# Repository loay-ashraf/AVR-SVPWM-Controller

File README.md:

# AVR SVPWM Controller
SVPWM controller prototype implemented using AVR 8-bit microcontroller as a part of EV car conversion graduation project for Mechatronics Engineering Bachelor - Fall 2018.

## Overview
This section gives an overview of the system.

### Concept
Space vector pulse width modulation (SVPWM) is an algorithm for the control of pulse width modulation (PWM).

It is used for the creation of alternating current (AC) waveforms; most commonly to drive 3 phase AC powered motors at varying speeds from DC using multiple MOSFET/IGBT transistors. 

### System Layout
System is divided into two separate modules that communicate with each other to acheive the desired output, which are:

#### Pilot Module

Pilot module receives operating parameters from co-pilot (output frequency) and then outputs PWM signals to IGBT bridge, also it checks for current fault signal and in case of current overload it shuts down waiting for a manual reset.

#### Co-Pilot Module

Co-Pilot module reads user input via rotary potentiometer for output frequency, current sensor for current overload signal, then sends operating parameters to Pilot module and finally outputs system status (frequency, RPM, current,...etc.) to a character LCD.

## Discussion
This section discusses desicions made regarding design and implementation.

### Microcontroller

1. We opted for ATmega128 for pilot module as it runs at 16MHZ frequency and also has two 16-bit timers each having three output compare pins.
2. We opted for ATmega32 for co-pilot module as it runs at 16MHZ frequency and has enough pins for interfacing character LCD and current sensors via ADC.

### Communication Protocol

It is found that best communcation type (protocol) for such system would be a parallel communication bus because of the following reasons:

- Distance between modules is so short (<5m)
- Data sent is time senstive
- Pilot module is starving for CPU clock cycles to calculate and update timer's compare registers values and going with parallel would be ideal for this situation as it only costs one CPU clock cycle to read PINx register 

So we opted for an 8-bit wide parallel communication bus (including READY and ACK signals) which would be much faster than any serial communication available (USART, I2C and SPI).

### Timer Mode

We used Phase and Frequency correct PWM mode with ICR1 as TOP value as it mimics the center aligned PWM mode required for the space vector algorithm.

## Sample Output

### Non-Filtered Output

Below is the ouput of the system without attaching low pass LC filter:

### Filtered Output

Below is the output of the system with low pass LC filter attached:

## Built With
- Atmel Studio 7 - The official AVR IDE
- AVR-gcc V5.4 - C compiler
- GNU Make - auto-generated makefile
- CadSoft EAGLE - PCB design tool

## Authors
Loay Ashraf - <loay.ashraf.96@gmail.com>

Mohamed Gamal - <muhammed.gamal051@gmail.com>

## License
This project is licensed under the MIT License - see the LICENSE.md file for details

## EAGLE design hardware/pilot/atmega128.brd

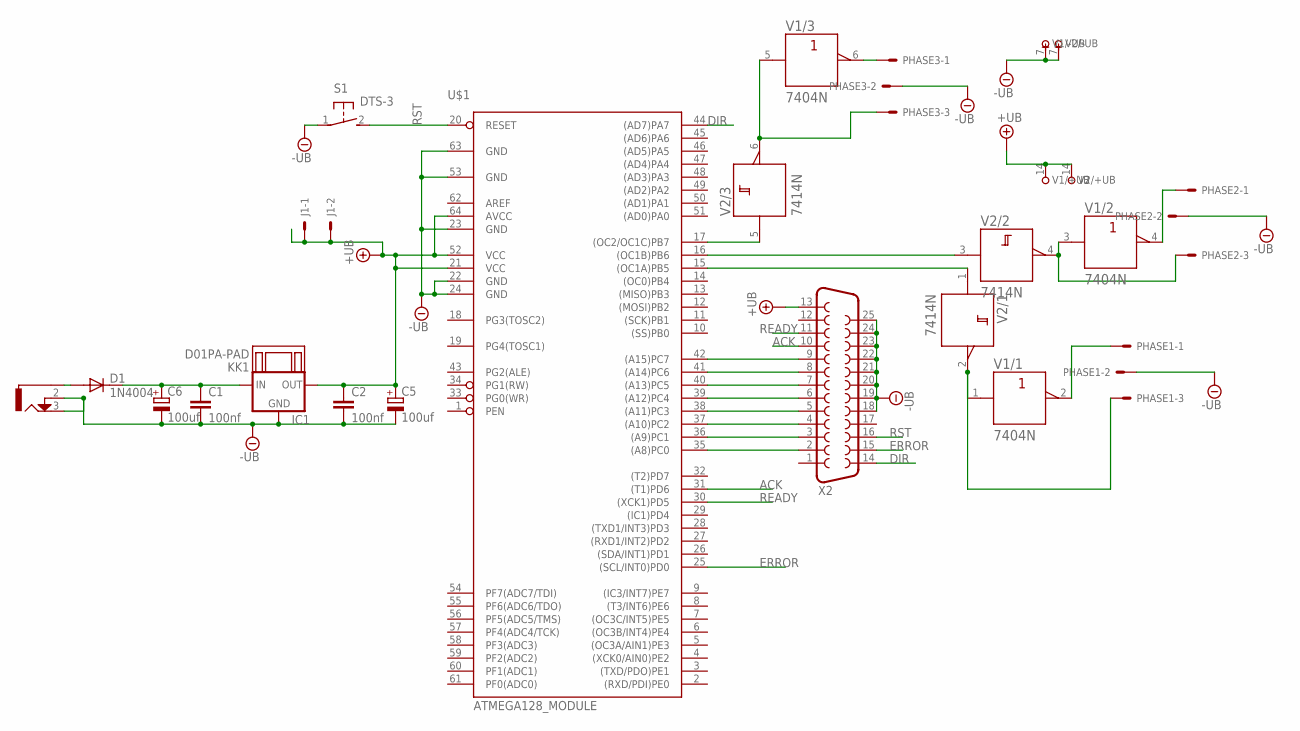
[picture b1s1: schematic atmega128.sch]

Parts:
C1, C2: 100nf; C025-025X050
C5, C6: 100uf; E2,5-6
D1: 1N4004; DO41-10
IC1: 78XXS
J1: 22-27-2021-02; 6410-02
KK1: D01PA-PAD
PHASE1, PHASE2, PHASE3: 6410-03
S1: DTS-3
U$1: ATMEGA128_MODULE
U$2: DC-21MM
V1: 7404N; DIL14
V2: 7414N; DIL14
X2: F25HP

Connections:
+UB: C2.1, C5.+, IC1.OUT, J1.1, J1.2, U$1.21 (VCC), U$1.52 (VCC), U$1.64 (AVCC), V1.14 (+UB), V2.14 (+UB), X2.13
-UB: C1.2, C2.2, C5.-, C6.-, IC1.GND, PHASE1.2, PHASE2.2, PHASE3.2, S1.1, U$1.22 (GND), U$1.23 (GND), U$1.24 (GND), U$1.53 (GND), U$1.63 (GND), U$2.2, U$2.3, V1.7 (-UB), V2.7 (-UB), X2.18, X2.19, X2.20, X2.21, X2.22, X2.23, X2.24, X2.25
ACK: U$1.31 ((T1)PD6), X2.10
DIR: U$1.44 ((AD7)PA7), X2.14
ERROR: U$1.25 ((SCL/INT0)PD0), X2.15
unnamed: D1.A, U$2.1
unnamed: C1.1, C6.+, D1.C, IC1.IN
unnamed: U$1.42 ((A15)PC7), X2.9
unnamed: U$1.41 ((A14)PC6), X2.8
unnamed: U$1.40 ((A13)PC5), X2.7
unnamed: U$1.39 ((A12)PC4), X2.6
unnamed: U$1.38 ((A11)PC3), X2.5
unnamed: U$1.37 ((A10)PC2), X2.4
unnamed: U$1.36 ((A9)PC1), X2.3
unnamed: U$1.35 ((A8)PC0), X2.2
PHASE1: U$1.15 ((OC1A)PB5), V2.1 (A)
PHASE1HIGH: PHASE1.1, V1.2 (Y)
PHASE1LOW: PHASE1.3, V1.1 (A), V2.2 (Y)
PHASE2: U$1.16 ((OC1B)PB6), V2.3 (A)
PHASE2HIGH: PHASE2.1, V1.4 (Y)
PHASE2LOW: PHASE2.3, V1.3 (A), V2.4 (Y)
PHASE3: U$1.17 ((OC2/OC1C)PB7), V2.5 (A)
PHASE3HIGH: PHASE3.1, V1.6 (Y)
PHASE3LOW: PHASE3.3, V1.5 (A), V2.6 (Y)
READY: U$1.30 ((XCK1)PD5), X2.11
RST: S1.2, U$1.20 (RESET), X2.16

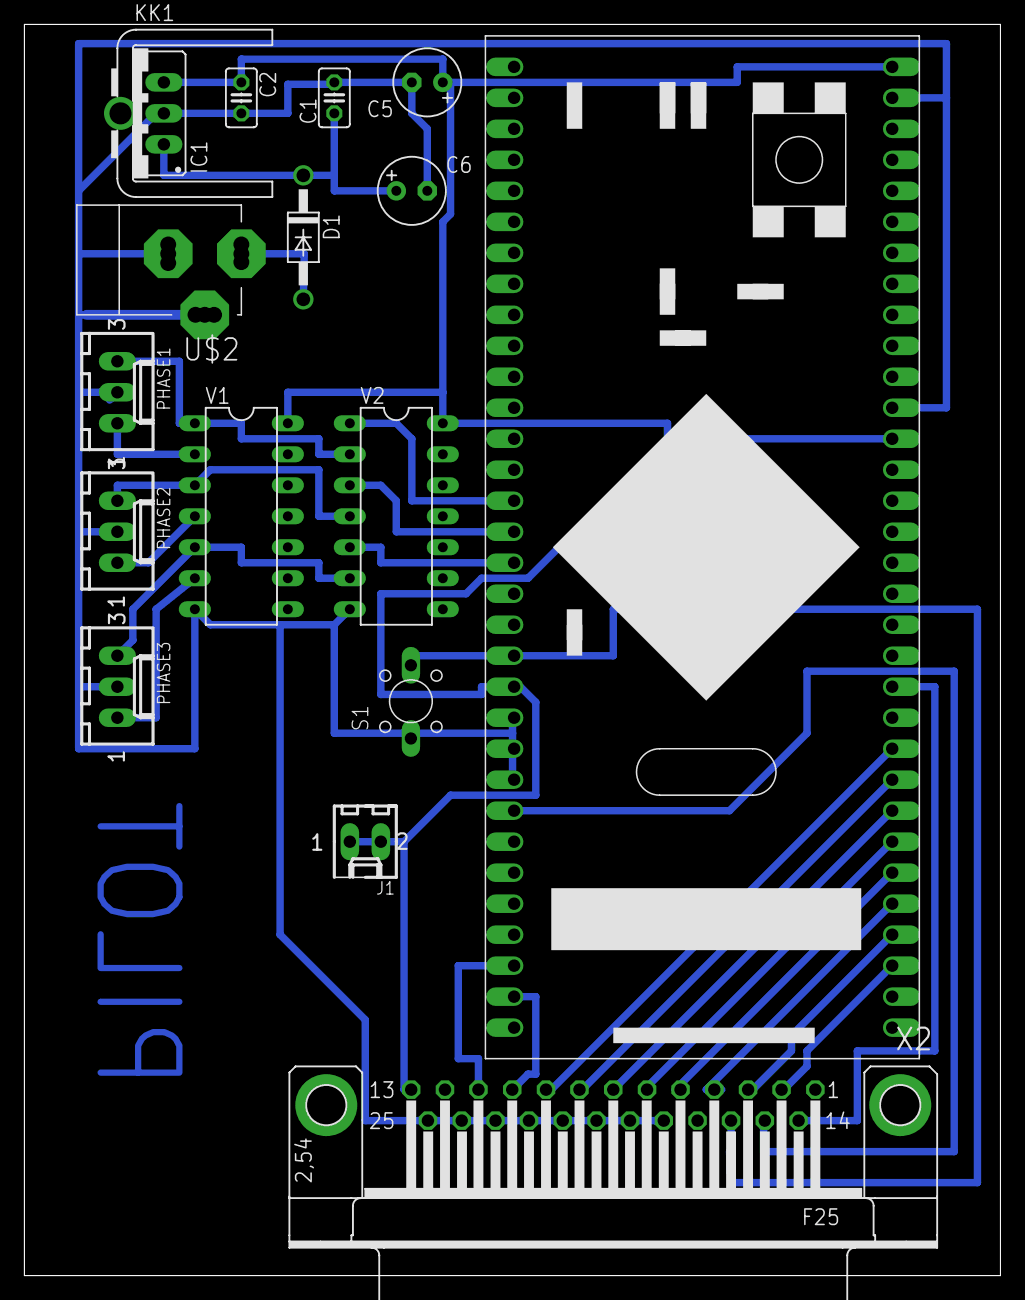
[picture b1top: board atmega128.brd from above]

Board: 2 copper layers, 80.0 x 102.5 mm, 17 parts (0 on the bottom side), 26 nets.

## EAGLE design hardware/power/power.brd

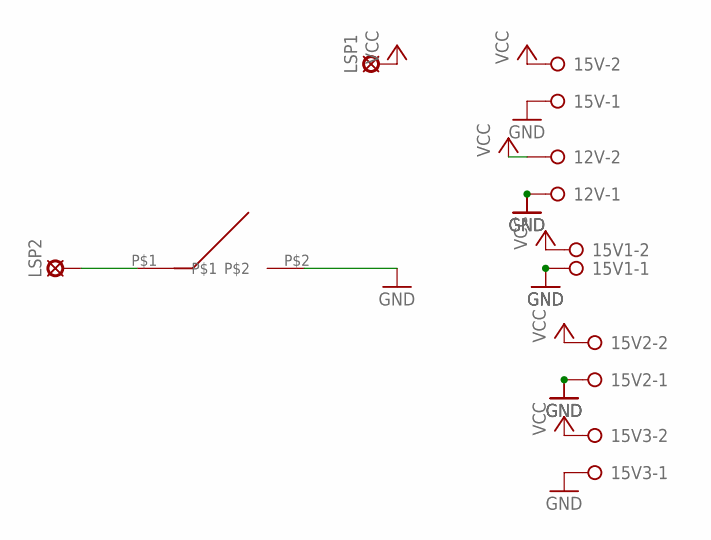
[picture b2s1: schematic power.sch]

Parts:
12V, 15V, 15V1, 15V2, 15V3: W237-02P; W237-132
LSP1, LSP2: SE14
U$1: ON/OFF

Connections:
GND: 12V.1, 15V.1, 15V1.1, 15V2.1, 15V3.1, U$1.P$2
unnamed: LSP2.MP, U$1.P$1
VCC: 12V.2, 15V.2, 15V1.2, 15V2.2, 15V3.2, LSP1.MP

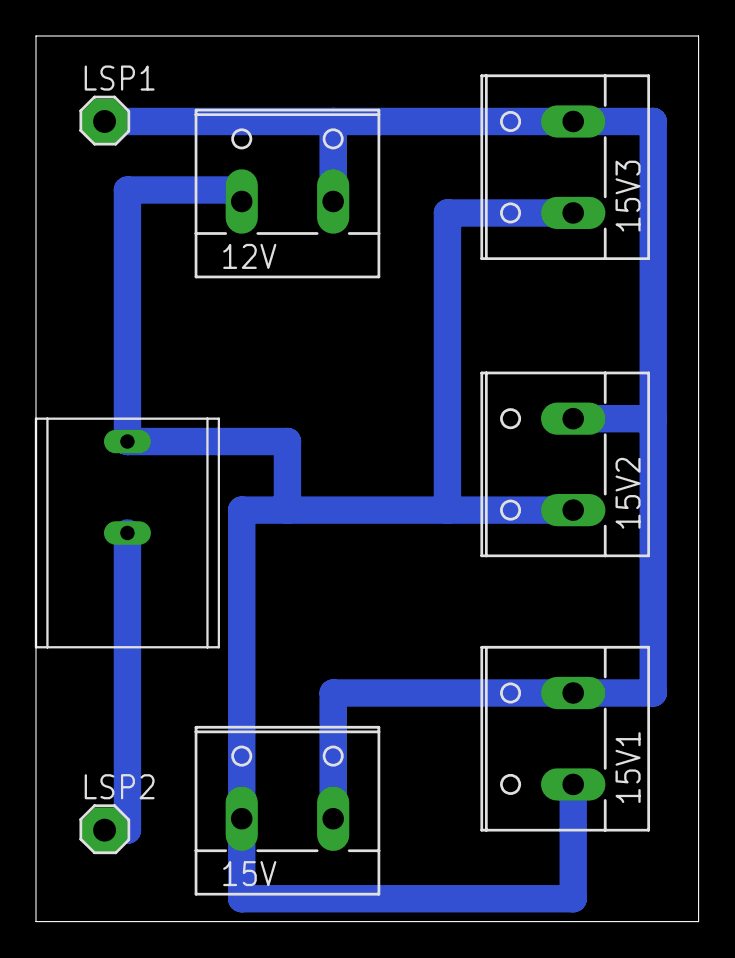
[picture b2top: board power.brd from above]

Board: 2 copper layers, 36.8 x 49.2 mm, 8 parts (0 on the bottom side), 3 nets.

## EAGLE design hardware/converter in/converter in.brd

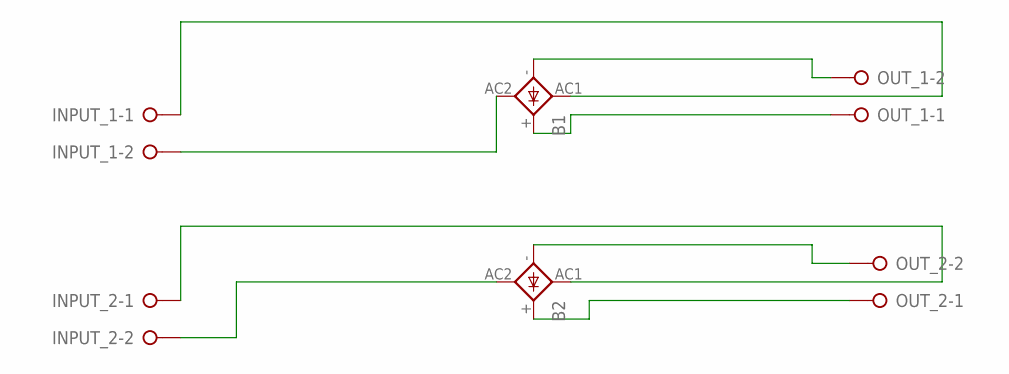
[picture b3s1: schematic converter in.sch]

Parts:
B1, B2: 2KBP
INPUT_1, INPUT_2: W237-02P; W237-132
OUT_1, OUT_2: W237-02P; W237-132

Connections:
unnamed: B1.-, OUT_1.2
unnamed: B1.+, OUT_1.1
unnamed: B2.-, OUT_2.2
unnamed: B2.+, OUT_2.1
unnamed: B2.AC1, INPUT_2.1
unnamed: B2.AC2, INPUT_2.2
unnamed: B1.AC2, INPUT_1.2
unnamed: B1.AC1, INPUT_1.1

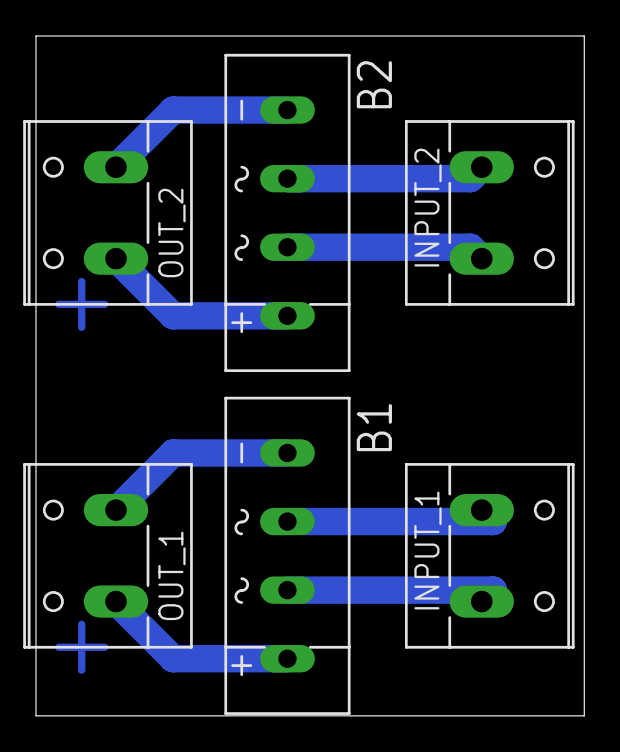
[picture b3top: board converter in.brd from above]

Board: 2 copper layers, 30.5 x 37.8 mm, 6 parts (0 on the bottom side), 8 nets.

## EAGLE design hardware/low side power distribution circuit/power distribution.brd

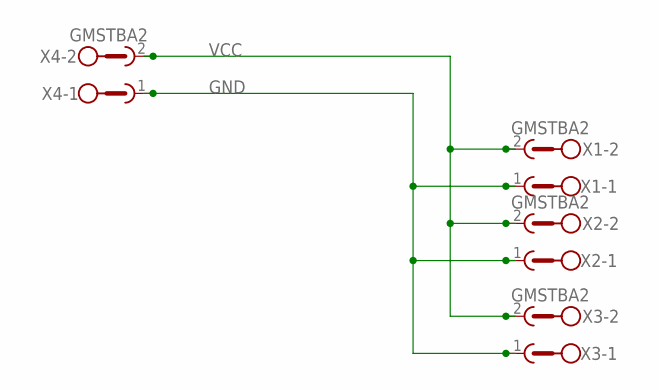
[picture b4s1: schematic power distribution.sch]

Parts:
X1, X2, X3, X4: GMSTBA2

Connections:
GND: X1.1, X2.1, X3.1, X4.1
VCC: X1.2, X2.2, X3.2, X4.2

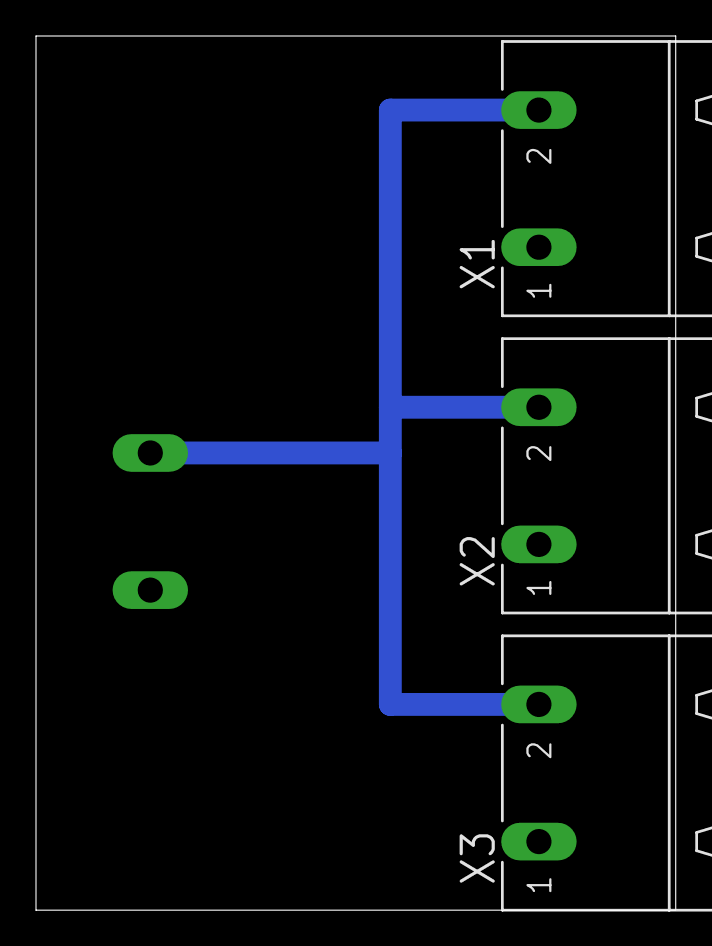
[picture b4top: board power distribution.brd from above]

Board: 2 copper layers, 35.5 x 48.6 mm, 4 parts (1 on the bottom side), 2 nets.

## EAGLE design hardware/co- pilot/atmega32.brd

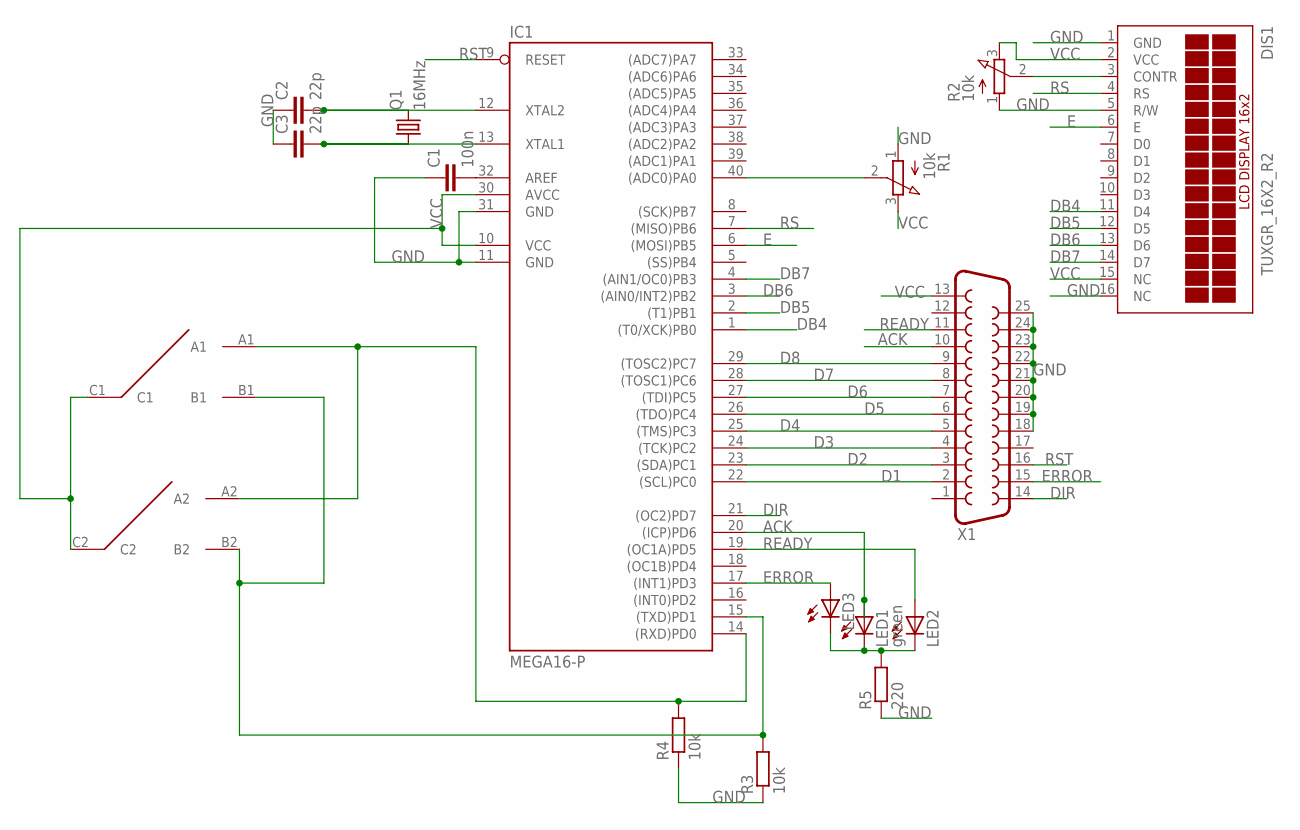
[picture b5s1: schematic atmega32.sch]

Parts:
C1: 100n; C025-025X050
C2, C3: 22p; C025-025X050
DIS1: TUXGR_16X2_R2
IC1: MEGA16-P; DIL40
LED1: green; LED3MM
LED2, LED3: LED3MM
Q1: 16MHz; HC49/S
R1, R2: 10k; 3RP/1610N
R3, R4: 10k; 0207/10
R5: 220; 0207/10
U$1: TOGGLE
X1: F25HP

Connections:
ACK: IC1.20 ((ICP)PD6), LED1.A, X1.10
D1: IC1.22 ((SCL)PC0), X1.2
D2: IC1.23 ((SDA)PC1), X1.3
D3: IC1.24 ((TCK)PC2), X1.4
D4: IC1.25 ((TMS)PC3), X1.5
D5: IC1.26 ((TDO)PC4), X1.6
D6: IC1.27 ((TDI)PC5), X1.7
D7: IC1.28 ((TOSC1)PC6), X1.8
D8: IC1.29 ((TOSC2)PC7), X1.9
DB4: DIS1.11 (D4), IC1.1 ((T0/XCK)PB0)
DB5: DIS1.12 (D5), IC1.2 ((T1)PB1)
DB6: DIS1.13 (D6), IC1.3 ((AIN0/INT2)PB2)
DB7: DIS1.14 (D7), IC1.4 ((AIN1/OC0)PB3)
DIR: IC1.21 ((OC2)PD7), X1.14
E: DIS1.6 (E), IC1.6 ((MOSI)PB5)
ERROR: IC1.17 ((INT1)PD3), LED3.A, X1.15
GND: C1.1, C2.1, C3.1, DIS1.1 (GND), DIS1.5 (R/W), DIS1.16 (NC), IC1.11 (GND), IC1.31 (GND), R1.1 (A), R2.1 (A), R3.1, R4.1, R5.1, X1.18, X1.19, X1.20, X1.21, X1.22, X1.23, X1.24, X1.25
unnamed: LED1.K (C), LED2.K (C), LED3.K (C), R5.2
unnamed: IC1.14 ((RXD)PD0), R4.2, U$1.A1, U$1.A2
unnamed: IC1.15 ((TXD)PD1), R3.2, U$1.B1, U$1.B2
unnamed: C2.2, IC1.12 (XTAL2), Q1.2
unnamed: IC1.40 ((ADC0)PA0), R1.2 (S)
unnamed: C1.2, IC1.32 (AREF)
unnamed: C3.2, IC1.13 (XTAL1), Q1.1
unnamed: DIS1.3 (CONTR), R2.2 (S)
READY: IC1.19 ((OC1A)PD5), LED2.A, X1.11
RS: DIS1.4 (RS), IC1.7 ((MISO)PB6)
RST: IC1.9 (RESET), X1.16
VCC: DIS1.2 (VCC), DIS1.15 (NC), IC1.10 (VCC), IC1.30 (AVCC), R1.3 (E), R2.3 (E), U$1.C1, U$1.C2, X1.13

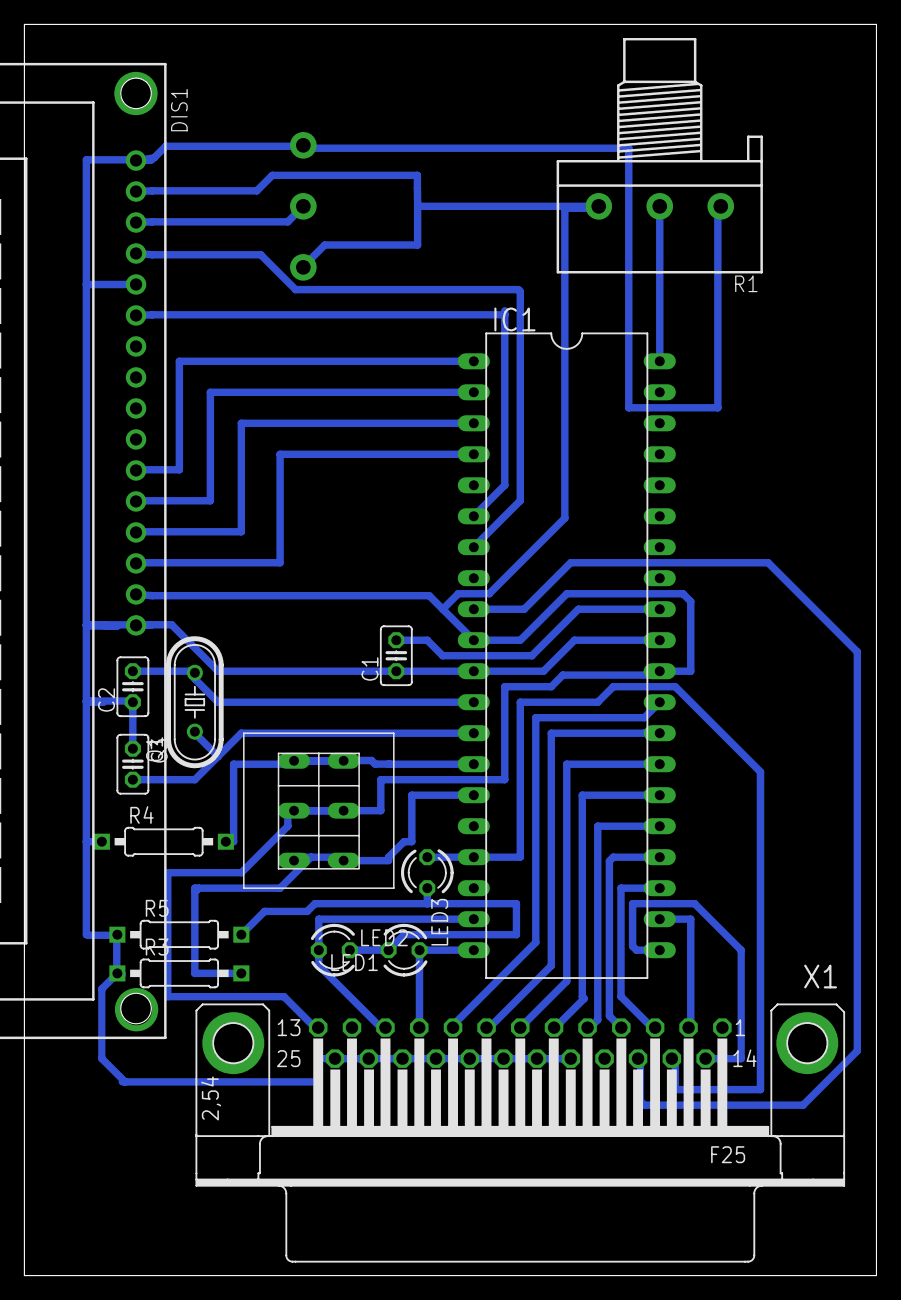
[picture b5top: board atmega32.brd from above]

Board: 2 copper layers, 69.8 x 102.5 mm, 16 parts (1 on the bottom side), 29 nets.

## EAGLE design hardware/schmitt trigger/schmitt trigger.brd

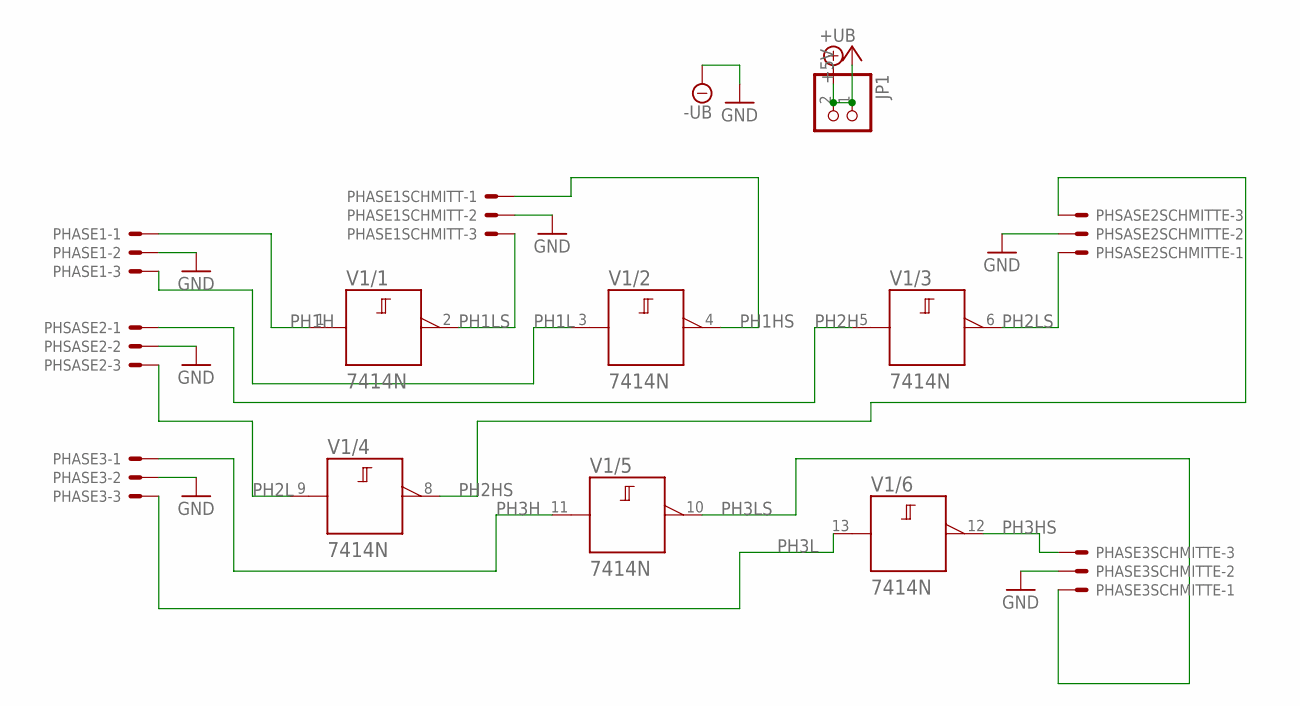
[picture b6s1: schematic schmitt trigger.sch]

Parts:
JP1: PINHD-1X2; 1X02
PHASE1, PHASE1SCHMITT, PHASE3, PHASE3SCHMITTE: 22-23-2031
PHSASE2, PHSASE2SCHMITTE: 22-23-2031
V1: 7414N; DIL14

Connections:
+5V: JP1.1, JP1.2, V1.14 (+UB)
GND: PHASE1.2, PHASE1SCHMITT.2, PHASE3.2, PHASE3SCHMITTE.2, PHSASE2.2, PHSASE2SCHMITTE.2, V1.7 (-UB)
PH1H: PHASE1.1, V1.1 (A)
PH1HS: PHASE1SCHMITT.1, V1.4 (Y)
PH1L: PHASE1.3, V1.3 (A)
PH1LS: PHASE1SCHMITT.3, V1.2 (Y)
PH2H: PHSASE2.1, V1.5 (A)
PH2HS: PHSASE2SCHMITTE.3, V1.8 (Y)
PH2L: PHSASE2.3, V1.9 (A)
PH2LS: PHSASE2SCHMITTE.1, V1.6 (Y)
PH3H: PHASE3.1, V1.11 (A)
PH3HS: PHASE3SCHMITTE.3, V1.12 (Y)
PH3L: PHASE3.3, V1.13 (A)
PH3LS: PHASE3SCHMITTE.1, V1.10 (Y)

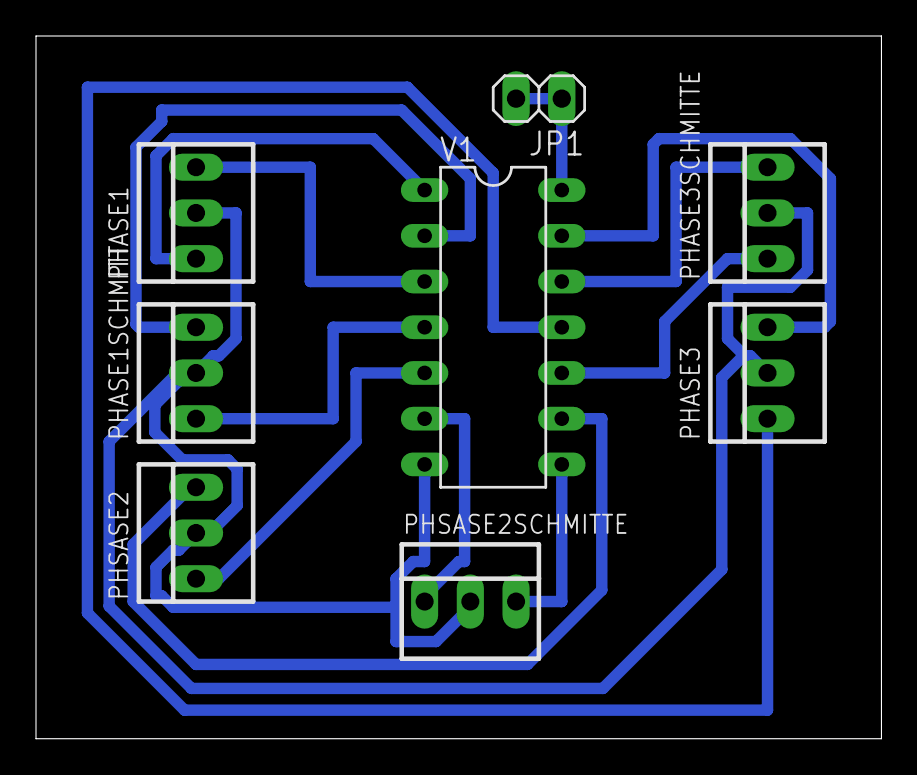
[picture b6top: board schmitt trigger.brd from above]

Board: 2 copper layers, 47.0 x 39.0 mm, 8 parts (0 on the bottom side), 14 nets.

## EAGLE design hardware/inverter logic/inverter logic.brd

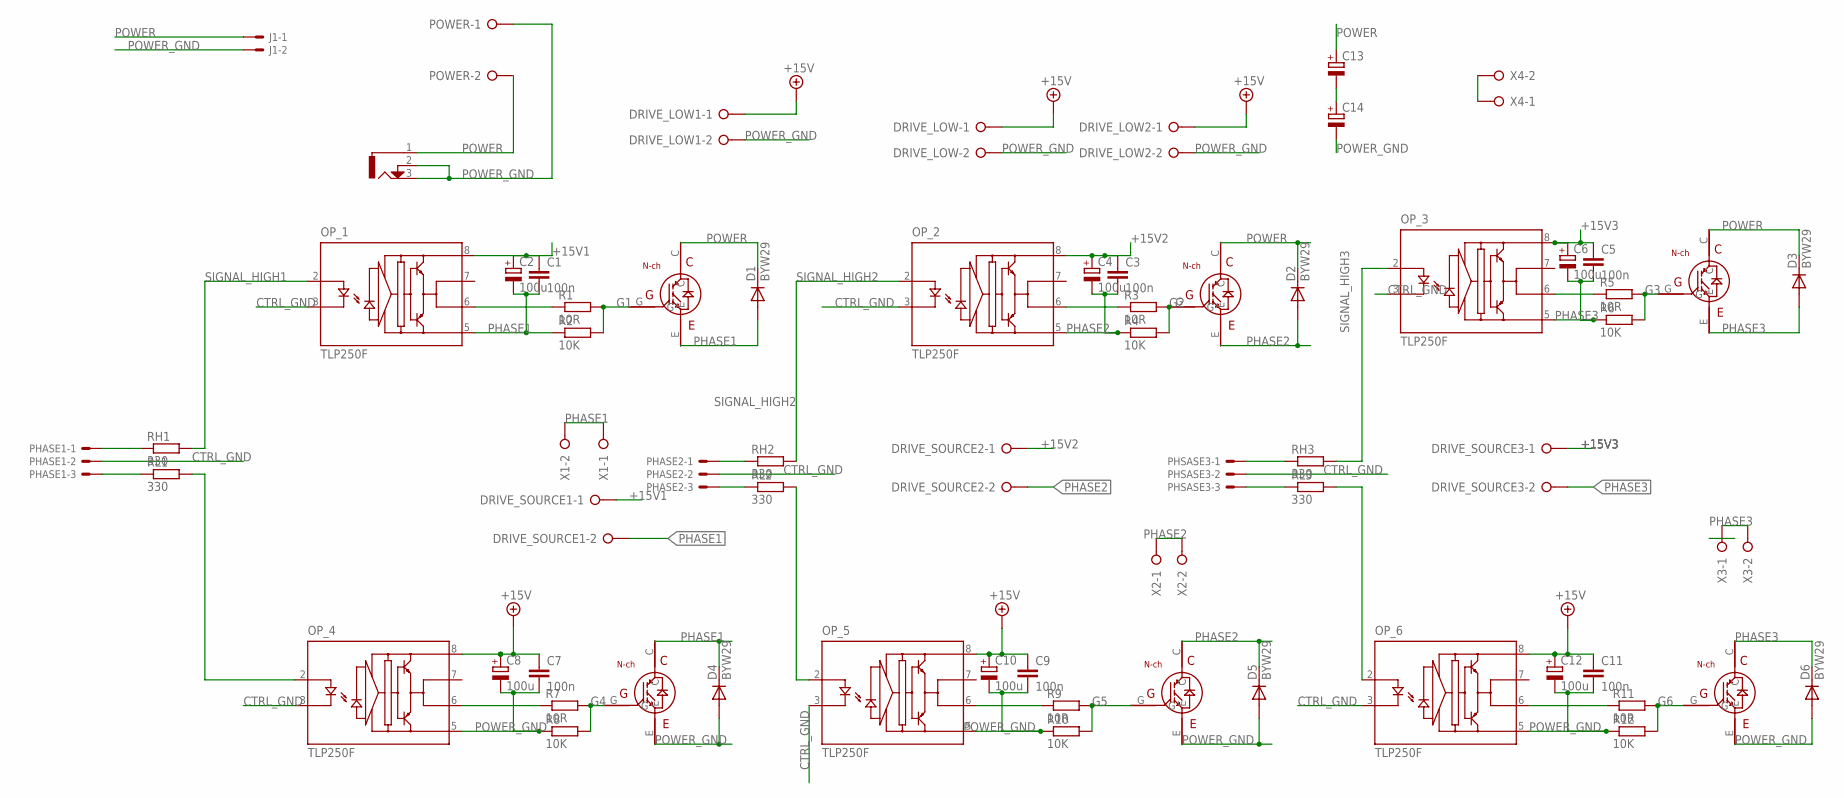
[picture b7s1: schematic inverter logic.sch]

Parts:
C1, C3, C5, C7, C9, C11: 100n; C025-025X050
C2, C4, C6, C8, C10, C12: 100u; E2,5-6
C13, C14: CPOL-EUE2.5-6; E2,5-6
D1, D2, D3, D4, D5, D6: BYW29; DO220S
DRIVE_LOW, DRIVE_LOW1, DRIVE_LOW2: W237-02P; W237-132
DRIVE_SOURCE1, DRIVE_SOURCE2, DRIVE_SOURCE3: W237-02P; W237-132
J1: 22-27-2021-02; 6410-02
OP_1, OP_2, OP_3, OP_4, OP_5, OP_6: TLP250F; DIL08
PHASE1, PHASE2: 22-27-2031-03; 6410-03
PHSASE3: 22-27-2031-03; 6410-03
POWER: W237-02P; W237-132
R1, R3, R5, R7, R9, R11: 10R; 0207/10
R2, R4, R6, R8, R10, R12: 10K; 0207/10
RH1, RH2, RH3: 330; 0207/10
RL1, RL2, RL3: 330; 0207/10
T1, T2, T3, T4, T5, T6: TO-247A; TO-247
U$1: DC-21MM
X1, X2, X3, X4: W237-02P; W237-132

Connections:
+15V: C7.1, C8.+, C9.1, C10.+, C11.1, C12.+, DRIVE_LOW.1, DRIVE_LOW1.1, DRIVE_LOW2.1, OP_4.8 (VCC), OP_5.8 (VCC), OP_6.8 (VCC)
+15V1: C1.1, C2.+, DRIVE_SOURCE1.1, OP_1.8 (VCC)
+15V2: C3.1, C4.+, DRIVE_SOURCE2.1, OP_2.8 (VCC)
+15V3: C5.1, C6.+, DRIVE_SOURCE3.1, OP_3.8 (VCC)
CTRL_GND: OP_1.3 (K), OP_2.3 (K), OP_3.3 (K), OP_4.3 (K), OP_5.3 (K), OP_6.3 (K), PHASE1.2, PHASE2.2, PHSASE3.2
G1: R1.2, R2.2, T1.G
G2: R3.2, R4.2, T2.G
G3: R5.2, R6.2, T3.G
G4: R7.2, R8.2, T4.G
G5: R9.2, R10.2, T5.G
G6: R11.2, R12.2, T6.G
N: C13.-, C14.+, X4.1, X4.2
unnamed: PHASE1.3, RL1.1
unnamed: PHASE2.3, RL2.1
unnamed: PHSASE3.3, RL3.1
unnamed: PHASE2.1, RH2.1
unnamed: PHSASE3.1, RH3.1
unnamed: OP_3.6 (VO), R5.1
unnamed: PHASE1.1, RH1.1
unnamed: OP_1.6 (VO), R1.1
unnamed: OP_2.6 (VO), R3.1
unnamed: OP_4.6 (VO), R7.1
unnamed: OP_5.6 (VO), R9.1
unnamed: OP_6.6 (VO), R11.1
PHASE1: C1.2, C2.-, D1.A, D4.C, DRIVE_SOURCE1.2, OP_1.5 (GND), R2.1, T1.E, T4.C, X1.1, X1.2
PHASE2: C3.2, C4.-, D2.A, D5.C, DRIVE_SOURCE2.2, OP_2.5 (GND), R4.1, T2.E, T5.C, X2.1, X2.2
PHASE3: C5.2, C6.-, D3.A, D6.C, DRIVE_SOURCE3.2, OP_3.5 (GND), R6.1, T3.E, T6.C, X3.1, X3.2
POWER: C13.+, D1.C, D2.C, D3.C, J1.1, POWER.2, T1.C, T2.C, T3.C, U$1.1
POWER_GND: C7.2, C8.-, C9.2, C10.-, C11.2, C12.-, C14.-, D4.A, D5.A, D6.A, DRIVE_LOW.2, DRIVE_LOW1.2, DRIVE_LOW2.2, J1.2, OP_4.5 (GND), OP_5.5 (GND), OP_6.5 (GND), POWER.1, R8.1, R10.1, R12.1, T4.E, T5.E, T6.E, U$1.2, U$1.3
SIGNAL_HIGH1: OP_1.2 (A), RH1.2
SIGNAL_HIGH2: OP_2.2 (A), RH2.2
SIGNAL_HIGH3: OP_3.2 (A), RH3.2
SIGNAL_LOW1: OP_4.2 (A), RL1.2
SIGNAL_LOW2: OP_5.2 (A), RL2.2
SIGNAL_LOW3: OP_6.2 (A), RL3.2

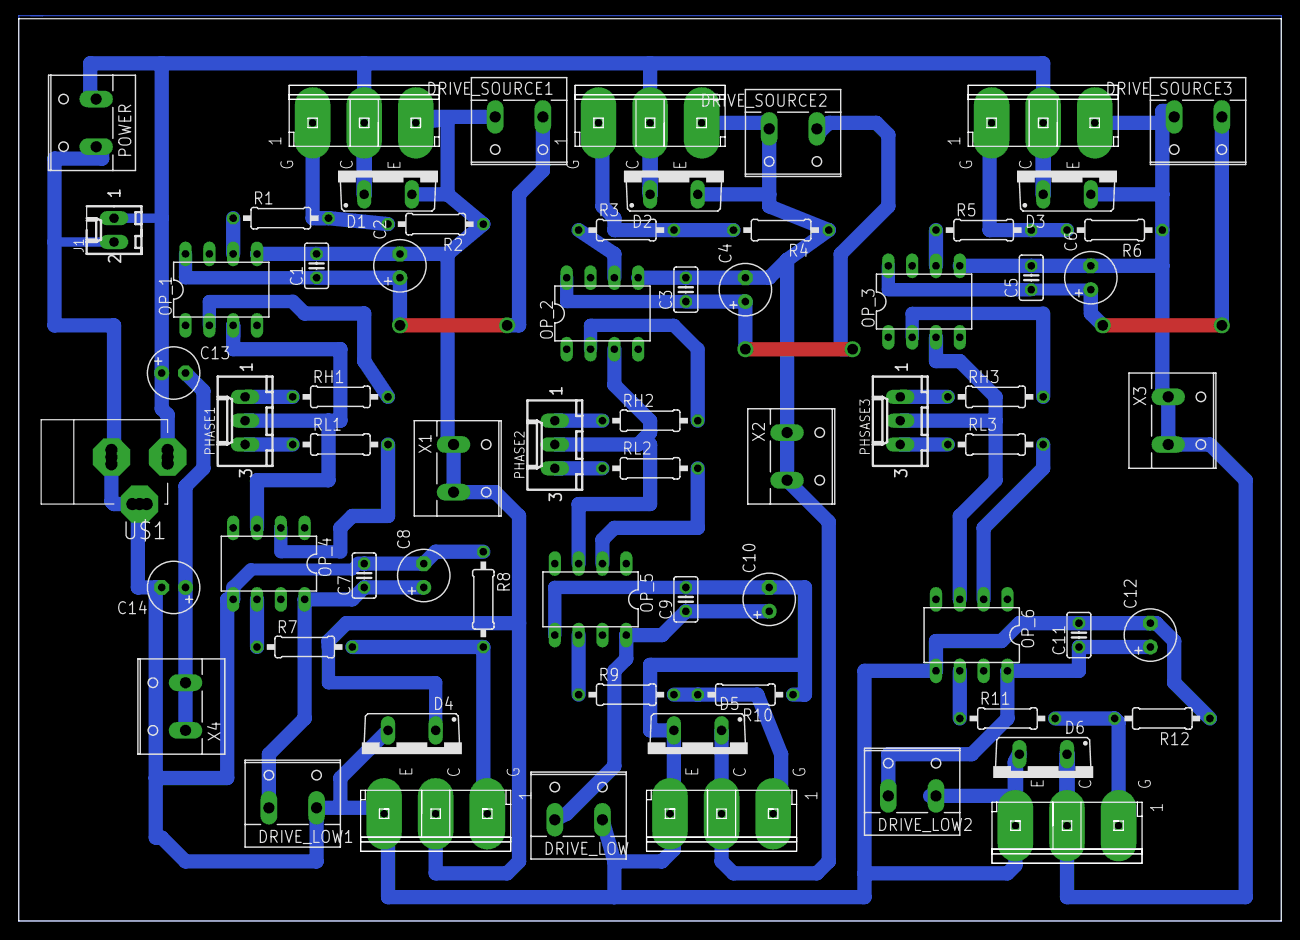
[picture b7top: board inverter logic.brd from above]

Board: 2 copper layers, 134.5 x 96.1 mm, 66 parts (0 on the bottom side), 35 nets.

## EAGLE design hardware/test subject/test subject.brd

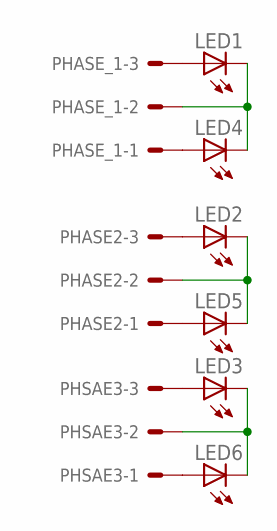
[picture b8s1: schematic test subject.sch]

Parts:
LED1, LED2, LED3, LED4, LED5, LED6: LED5MM
PHASE2: 22-27-2031-03; 6410-03
PHASE_1: 22-27-2031-03; 6410-03
PHSAE3: 22-27-2031-03; 6410-03

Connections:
unnamed: LED1.A, PHASE_1.3
unnamed: LED4.A, PHASE_1.1
unnamed: LED5.A, PHASE2.1
unnamed: LED2.A, PHASE2.3
unnamed: LED6.A, PHSAE3.1
unnamed: LED3.A, PHSAE3.3
unnamed: LED1.K (C), LED4.K (C), PHASE_1.2
unnamed: LED2.K (C), LED5.K (C), PHASE2.2
unnamed: LED3.K (C), LED6.K (C), PHSAE3.2

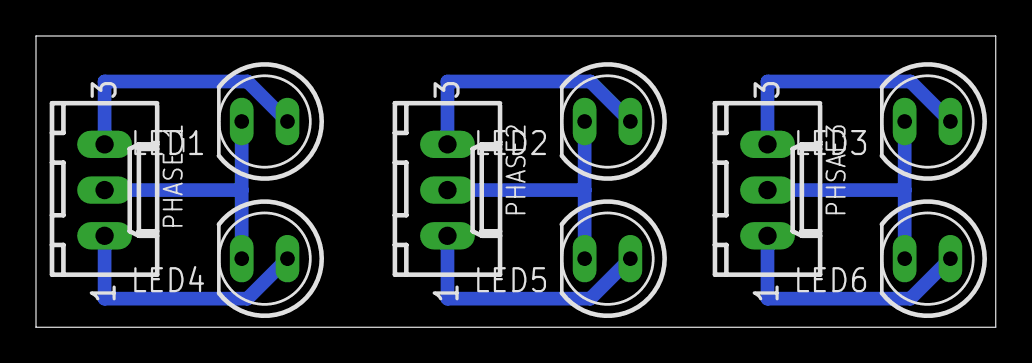
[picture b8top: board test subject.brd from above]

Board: 2 copper layers, 53.3 x 16.2 mm, 9 parts (0 on the bottom side), 9 nets.

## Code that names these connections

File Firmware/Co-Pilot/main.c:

/** @mainpage About
 *  @author Loay Ashraf <loay.ashraf.96@gmail.com>
 *  @version 1.0.0 
 *
 *  This program is implemented on ATmega16/32 running 
 *	at 16 MHZ CPU clock; it basically processes and shows 
 *	current inverter status like Voltage, Frequency 
 *  and the speed of the motor and sets the main controller 
 *	output by communicating via parallel bus using 8-bit 
 *	data line, one ACK line and one READY line; It also 
 *	interfaces 16x2 parallel interface character LCD 
 *	as an output. 
 *	
 *	@pinassignments	
 *	
 *	- PA0: Speed Potentiometer signal
 *	- PA1-3: Phases current signal
 *	- PB0-3: LCD 4-bit Data signal
 *	- PB5: LCD EN signal
 *	- PB6: LCD RS signal
 *	- PB7: Direction Data signal
 *	- PC0-7: Parallel bus 8-bit Data signal
 *	- PD0-1: Direction Switch signal
 *	- PD3: Current Overload ERROR signal
 *	- PD5: Parallel bus READY signal
 *	- PD6: Parallel bus ACK signal	
 *  
 *	@see main.c
 */


/** @file main.c
 *  @brief includes the main function
 *  
 *  the main function acquires data like set Voltage, Phases current,
 *	Direction, etc.; and it sends that data to the LCD and the main 
 *	controller over the parallel bus and sends an ERROR signal if any
 *	current overload happens for any of the 3 phases.
 *
 *  @author Loay Ashraf
 *	@version 1.0.0
 *  @pre include ADC.h, LCD.h, math.h and set F_CPU in micro_config.h
 *  @bug no known bugs
 *  @see micro_config.h
 */

//------------INCLUDE DEVICE DRIVERS------------//

#include "ADC.h"
#include "LCD.h"

//------------DEFINE DATA CALCULATION PARAMETERS------------//

#define VF_SLOPE 0.13333
#define MAX_VOLT 12
#define MIN_VOLT 0.2
#define AMMETER_VOLT 0.35 
#define RESISTOR_VALUE 1
#define CURRENT_THRESHOLD 2

//------------DECLARE GLOBAL VARIABLES------------//

/** @var float Volt
 *  @brief Stores current set Volt value
 */

/** @var float prev_Volt
 *  @brief Stores previous set Volt value to check for change
 */

 /** @var float Freq
 *  @brief Stores current commutation frequency
 */
 
 /** @var float C_PHa
 *  @brief Stores current Phase A current value
 */
 
 /** @var float C_PHb
 *  @brief Stores current Phase B current value
 */
 
 /** @var float C_PHc
 *  @brief Stores current Phase C current value
 */
 
 /** @var uint8 ACK_Flag
 *  @brief Stores previous ACK value to check for change
 */
float Volt, prev_Volt, Freq, C_PHa, C_PHb, C_PHc; 
uint8 ACK_Flag;

/** @brief the main function
 *
 *  see main.c description
 *
 *  @return exit status (1 or 0)
 */
int main(void){
    
	//------------INITIALIZE I/O PORTS------------//
	
	DDRA = 0x00;	// ADC PORT	
	DDRB = 0xFF;	// LCD DATA PORT
	DDRC = 0xFF;	// PARALLEL DATA PORT
	DDRD = 0x28;	// DIRECTION SW AND ACK/READY/FAULT PORT
	
	//------------INITIALIZE ADC AND LCD------------//
	
	ADC_Init(AVCC, RIGHT_ADJ, 128);	// AVCC as Vref, right sdjuted result (10-bit), 128 prescaler
	ADC_Read(ADC0);
	ADC_Read(ADC1);
	ADC_Read(ADC2);
	ADC_Read(ADC3);
	LCD_init(BO, BO);
	LCD_set_cursor(0,4);
	LCD_write_string("Stopped");

    while (1){
		
		//------------ACQUIRE CURRENT ACK STATUS AND DATA VIA ADC------------//
		
		ACK_Flag = PIND & 0x40;	// ACK SIGNAL (PD6)
		
		if(PIND&0x01){		// SWITCH TERMINAL #1 (PD0)
			PORTB |= 0x80;	// DIRECTION SIGNAL (PB7)
			Volt = ((ADC_Read(ADC0)/1023.0)*MAX_VOLT);
			if(Volt < MIN_VOLT)
				Volt = MIN_VOLT;
		}else if(PIND&0x02){	// SWITCH TERMINAL #2 (PD1)
			PORTB &= ~0x80;		// DIRECTION SIGNAL (PB7)
			Volt = ((ADC_Read(ADC0)/1023.0)*MAX_VOLT);
			if(Volt < MIN_VOLT)
				Volt = MIN_VOLT;
		}else{
			Volt = 0;}
			
		C_PHa = (((ADC_Read(ADC1)/1023.0)*AMMETER_VOLT)/RESISTOR_VALUE);
		C_PHb = (((ADC_Read(ADC2)/1023.0)*AMMETER_VOLT)/RESISTOR_VALUE);
		C_PHc = (((ADC_Read(ADC3)/1023.0)*AMMETER_VOLT)/RESISTOR_VALUE);
		
		//------------CHECK FOR CURRENT FAULT------------//
		
		if(C_PHa > CURRENT_THRESHOLD || C_PHb > CURRENT_THRESHOLD || C_PHc > CURRENT_THRESHOLD){
			PORTD |= 0x08;	// FAULT SIGNAL (PD3)
			while(1);		// wait for manual reset
		}
		
		//------------CHECK IF NEW DATA IS RECIEVED------------//
		
		if(Volt == prev_Volt || fabs(Volt-prev_Volt) < 0.1)
		continue;
		
		//------------OUTPUT DATA TO LCD------------//
		
		if(Volt == 0 && !(PIND&0x01) && !(PIND&0x02)){
			LCD_clear();
			LCD_set_cursor(0,4);
			LCD_write_string("Stopped");
		}else{
			LCD_set_cursor(0,0);
			LCD_write_string("Voltage:");
			LCD_set_cursor(1,0);
			LCD_write_string("Frequency: ");
			LCD_set_cursor(0,8);
			LCD_write_float(Volt);
			LCD_write_string(" V");
			LCD_set_cursor(1,11);
			LCD_write_int(90);
			LCD_write_string(" HZ");
		}
		
		//------------SET READY FLAG AND SEND DATA------------//
		
		PORTD |= 0x20;		// READY SIGNAL (PD5)
		PORTC = (Volt*10);	// DATA PORTC
		
		//------------WAIT FOR THE PILOT TO RECIEVE THE DATA------------//
		
		while (ACK_Flag == (PIND&0x40));
		PORTD &= ~0x20;		// READY SIGNAL (PD5)
		prev_Volt = Volt;	
    }
}

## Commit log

2021-03-22 Add Firmware source files
